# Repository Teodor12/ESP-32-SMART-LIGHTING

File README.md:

An offline speech-recognition applicaton for the board ESP32-S3-DevKitC-1 and INMP441 I2S MEMS microphone.

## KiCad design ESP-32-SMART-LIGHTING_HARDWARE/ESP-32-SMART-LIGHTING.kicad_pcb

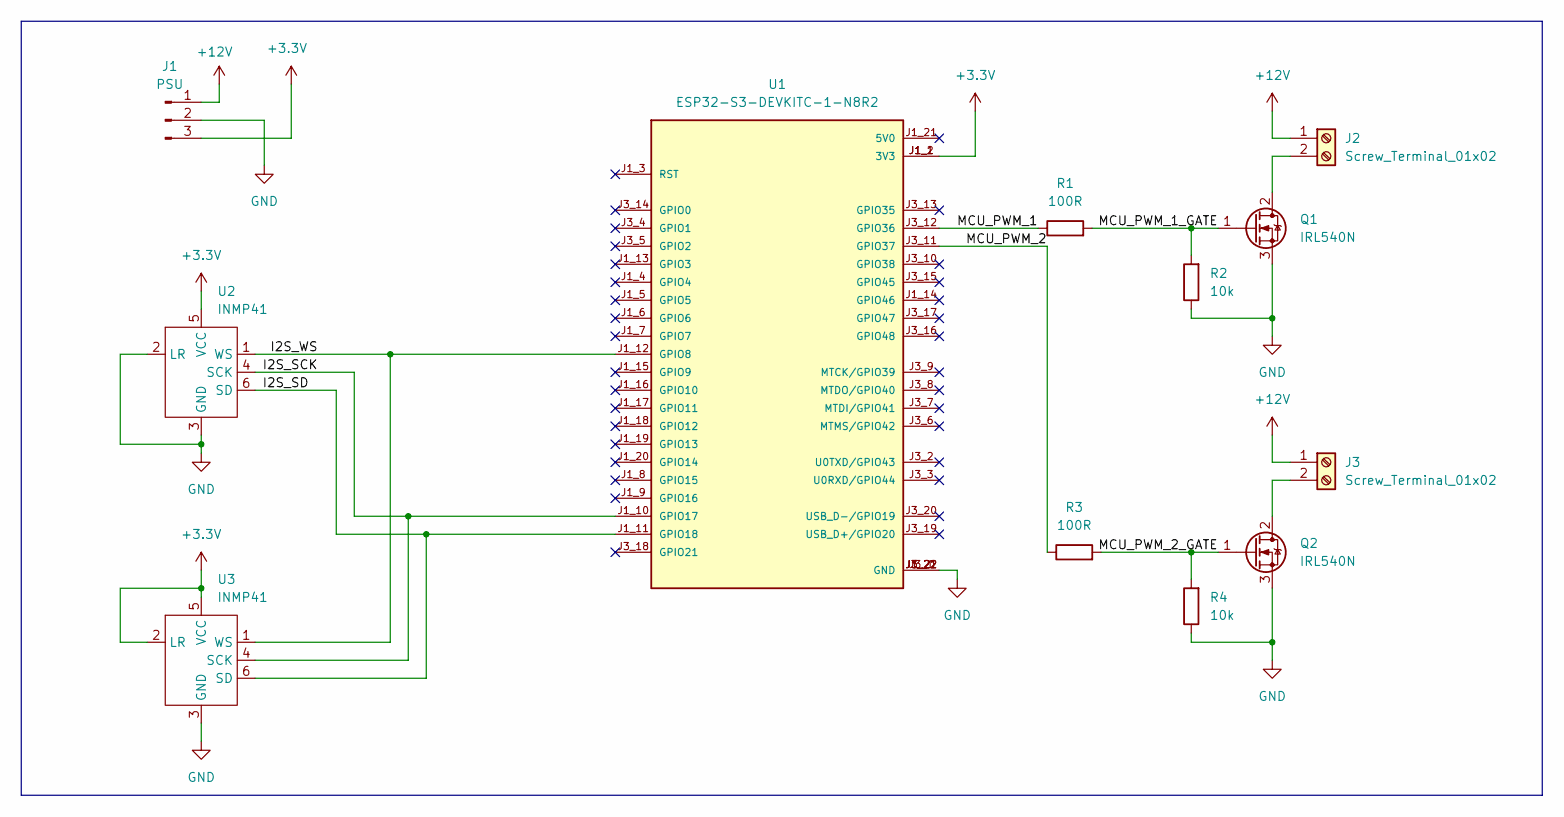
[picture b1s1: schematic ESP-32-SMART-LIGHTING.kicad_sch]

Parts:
J1: PSU; TerminalBlock_Xinya_XY308-2.54-3P_1x03_P2.54mm_Horizontal
J2, J3: Screw_Terminal_01x02; TerminalBlock_Xinya_XY308-2.54-2P_1x02_P2.54mm_Horizontal
Q1, Q2: IRL540N; TO-220-3_Vertical
R1, R3: 100R; R_Axial_DIN0204_L3.6mm_D1.6mm_P7.62mm_Horizontal
R2, R4: 10k; R_Axial_DIN0204_L3.6mm_D1.6mm_P7.62mm_Horizontal
U1: ESP32-S3-DEVKITC-1-N8R2; XCVR_ESP32-S3-DEVKITC-1-N8R2; PARTREV V1
U2, U3: INMP41

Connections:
+3.3V: J1.3, U1.J1_1 (3V3), U1.J1_2 (3V3), U2.5 (VCC), U3.2 (LR), U3.5 (VCC)
+12V: J1.1, J2.1, J3.1
/I2S_SCK: U1.J1_10 (GPIO17), U2.4 (SCK), U3.4 (SCK)
/I2S_SD: U1.J1_11 (GPIO18), U2.6 (SD), U3.6 (SD)
/I2S_WS: U1.J1_12 (GPIO8), U2.1 (WS), U3.1 (WS)
/MCU_PWM_1: R1.1, U1.J3_12 (GPIO36)
/MCU_PWM_1_GATE: Q1.1 (G), R1.2, R2.2
/MCU_PWM_2: R3.1, U1.J3_11 (GPIO37)
/MCU_PWM_2_GATE: Q2.1 (G), R3.2, R4.2
GND: J1.2, Q1.3 (S), Q2.3 (S), R2.1, R4.1, U1.J1_22 (GND), U1.J3_1 (GND), U1.J3_21 (GND), U1.J3_22 (GND), U2.2 (LR), U2.3 (GND), U3.3 (GND)
unnamed: J2.2, Q1.2 (D)
unnamed: J3.2, Q2.2 (D)

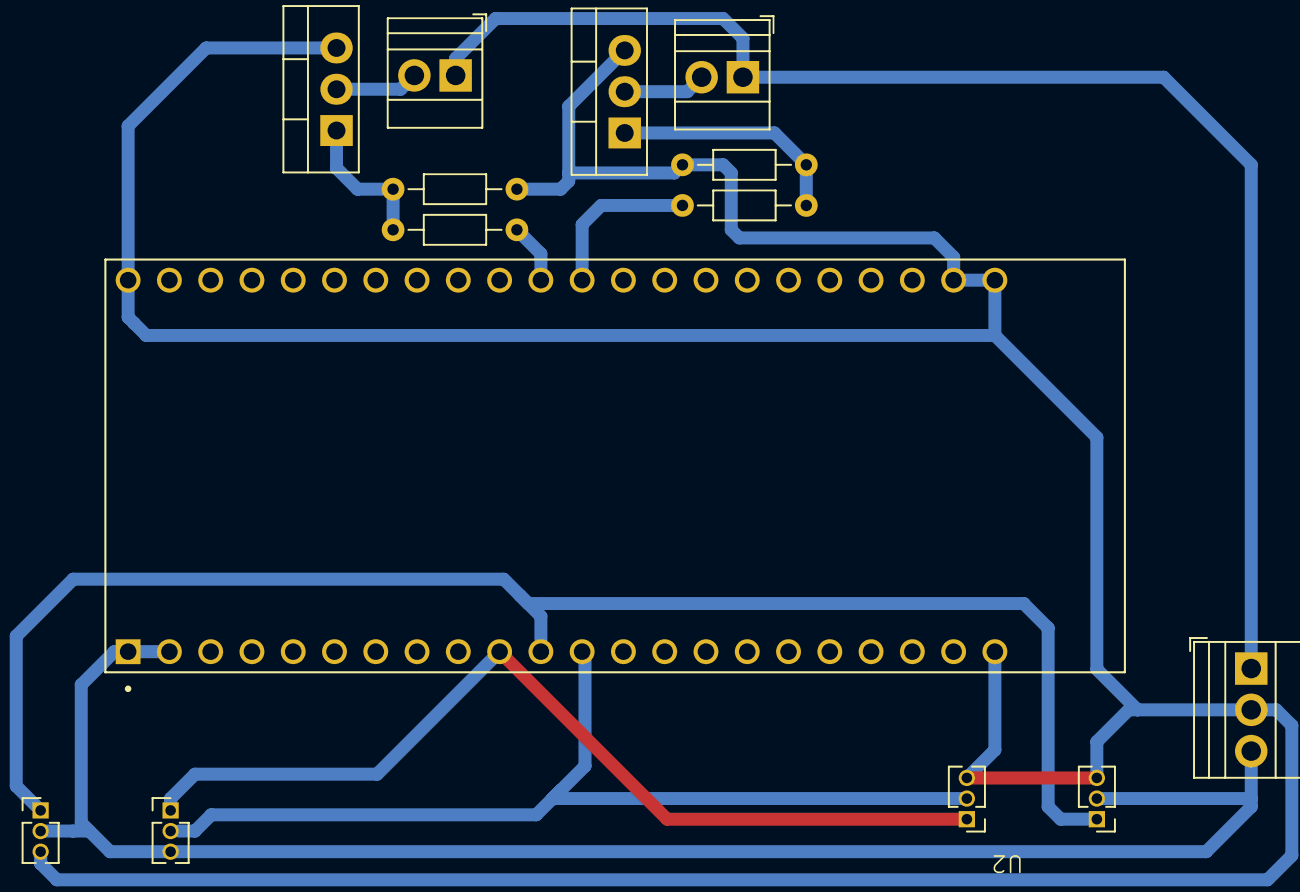
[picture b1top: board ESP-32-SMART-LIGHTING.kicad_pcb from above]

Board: 2 copper layers, 12 parts (0 on the bottom side), 12 nets.

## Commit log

2024-03-23 add gitignore
2024-03-23 add basic application
2024-03-29 update skdconfig
2024-03-29 add hardware_driver component
2024-03-29 set required components
2024-03-29 test i2s driver
2024-04-06 finish hardware_driver component
2024-04-06 add partition table and configure PSRAM
2024-04-06 add voice_assistant component to detect wakeword
2024-04-06 add voice_assistant to main makefile
2024-04-06 validate wakeword detection
2024-04-10 add README.md
2024-04-10 update i2s reading, fix sample numbers
2024-04-13 fix signed integer bit shifting
2024-04-13 add thread-safe task initialization
2024-04-14 replace the bit shifting in hardware driver
    The hardware driver (in the example project used for board ESP32-S3 EYE) shifts the microphone data right by 14
    places(the boards has a built-in INMP441 MEMS microphone chip). For further details check the comments in the
    example project.
2024-04-17 add Multinet and speech command configuration
2024-04-17 update detect_task to enable speech command recognition
2024-04-26 change wakenet model to 'Sophia'
2024-05-01 add led_strip idf-component
2024-05-01 add led_indicator component
2024-05-01 add delay to mutexes
2024-05-01 integrate led_indicator into wakeword detection
2024-06-06 add schematics for project
2024-06-06 change names and resistor values
2024-06-10 add 'pwm_output' component
2024-06-10 reduce polling time for initialization
2024-06-10 change partition sizes
2024-06-10 integrate pwm_output component
2024-06-10 add speech commands and change wakeword to 'Alexa'
2024-06-13 add external power supply
2024-07-04 add buckboost IC
2024-07-08 add word file
2024-07-08 update hash of led_strip component
2024-07-08 cleanup
2024-07-09 add PCM
2024-07-10 add LED, PWM, other items
2024-07-11 Add images of the circuit
2024-07-11 add first part of the circuit details
2024-07-13 add software environment description
2024-07-20 add led_indicator and pwm_output to docs
2024-07-20 add united formatting
2024-07-20 fix thread-safe initialization
2024-07-23 add esp-skainet and speech recognition
2024-07-24 finish Skainet and speech recognition
2024-07-27 add TOC
2024-07-28 add sources
2024-07-31 fix typos
2024-09-26 PCB desing
2024-09-29 Fixed PCB size, fixed module size
2024-11-17 fix hungarian typos
2024-11-17 remove page number from last page
2024-12-12 rename the obsolete word file
2024-12-12 add final word file
2024-12-12 update pronouncement
